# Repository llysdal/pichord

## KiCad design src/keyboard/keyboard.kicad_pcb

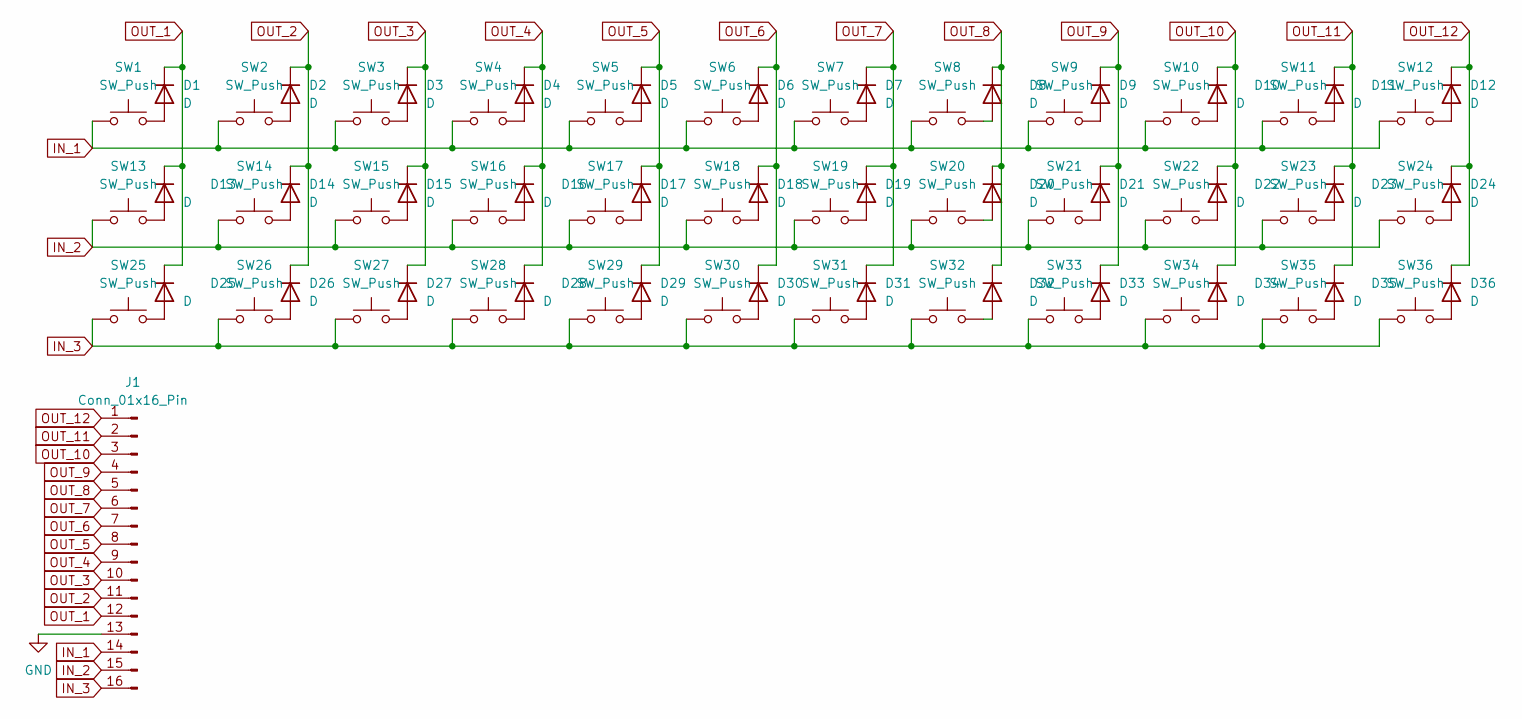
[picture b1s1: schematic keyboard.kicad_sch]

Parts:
D1, D2, D3, D4, D5, D6, D7, D8, D9, D10, D11, D12, D13, D14, D15, D16, D17, D18, D19, D20, D21, D22, D23, D24, D25, D26, D27, D28, D29, D30, D31, D32, D33, D34, D35, D36: D; D_DO-35_SOD27_P7.62mm_Horizontal
J1: Conn_01x16_Pin; PinHeader_2x08_P2.54mm_Vertical
SW1, SW2, SW3, SW4, SW5, SW6, SW7, SW8, SW9, SW10, SW11, SW12, SW13, SW14, SW15, SW16, SW17, SW18, SW19, SW20, SW21, SW22, SW23, SW24, SW25, SW26, SW27, SW28, SW29, SW30, SW31, SW32, SW33, SW34, SW35, SW36: SW_Push; Kailh_socket_MX_platemount

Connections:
GND: J1.13
IN_1: J1.14, SW1.1, SW2.1, SW3.1, SW4.1, SW5.1, SW6.1, SW7.1, SW8.1, SW9.1, SW10.1, SW11.1, SW12.1
IN_2: J1.15, SW13.1, SW14.1, SW15.1, SW16.1, SW17.1, SW18.1, SW19.1, SW20.1, SW21.1, SW22.1, SW23.1, SW24.1
IN_3: J1.16, SW25.1, SW26.1, SW27.1, SW28.1, SW29.1, SW30.1, SW31.1, SW32.1, SW33.1, SW34.1, SW35.1, SW36.1
unnamed: D1.2 (A), SW1.2
unnamed: D2.2 (A), SW2.2
unnamed: D3.2 (A), SW3.2
unnamed: D4.2 (A), SW4.2
unnamed: D5.2 (A), SW5.2
unnamed: D6.2 (A), SW6.2
unnamed: D7.2 (A), SW7.2
unnamed: D8.2 (A), SW8.2
unnamed: D9.2 (A), SW9.2
unnamed: D10.2 (A), SW10.2
unnamed: D11.2 (A), SW11.2
unnamed: D12.2 (A), SW12.2
unnamed: D13.2 (A), SW13.2
unnamed: D14.2 (A), SW14.2
unnamed: D15.2 (A), SW15.2
unnamed: D16.2 (A), SW16.2
unnamed: D17.2 (A), SW17.2
unnamed: D18.2 (A), SW18.2
unnamed: D19.2 (A), SW19.2
unnamed: D20.2 (A), SW20.2
unnamed: D21.2 (A), SW21.2
unnamed: D22.2 (A), SW22.2
unnamed: D23.2 (A), SW23.2
unnamed: D24.2 (A), SW24.2
unnamed: D25.2 (A), SW25.2
unnamed: D26.2 (A), SW26.2
unnamed: D27.2 (A), SW27.2
unnamed: D28.2 (A), SW28.2
unnamed: D29.2 (A), SW29.2
unnamed: D30.2 (A), SW30.2
unnamed: D31.2 (A), SW31.2
unnamed: D32.2 (A), SW32.2
unnamed: D33.2 (A), SW33.2
unnamed: D34.2 (A), SW34.2
unnamed: D35.2 (A), SW35.2
unnamed: D36.2 (A), SW36.2
OUT_1: D1.1 (K), D13.1 (K), D25.1 (K), J1.12
OUT_2: D2.1 (K), D14.1 (K), D26.1 (K), J1.11
OUT_3: D3.1 (K), D15.1 (K), D27.1 (K), J1.10
OUT_4: D4.1 (K), D16.1 (K), D28.1 (K), J1.9
OUT_5: D5.1 (K), D17.1 (K), D29.1 (K), J1.8
OUT_6: D6.1 (K), D18.1 (K), D30.1 (K), J1.7
OUT_7: D7.1 (K), D19.1 (K), D31.1 (K), J1.6
OUT_8: D8.1 (K), D20.1 (K), D32.1 (K), J1.5
OUT_9: D9.1 (K), D21.1 (K), D33.1 (K), J1.4
OUT_10: D10.1 (K), D22.1 (K), D34.1 (K), J1.3
OUT_11: D11.1 (K), D23.1 (K), D35.1 (K), J1.2
OUT_12: D12.1 (K), D24.1 (K), D36.1 (K), J1.1

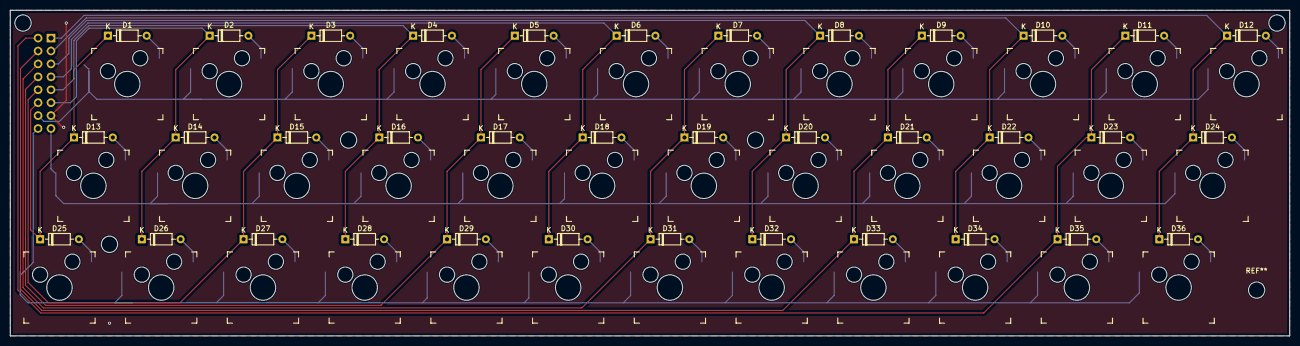
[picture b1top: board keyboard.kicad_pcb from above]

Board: 2 copper layers, 251.5 x 64.0 mm, 73 parts (1 on the bottom side), 51 nets.

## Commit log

2026-02-05 Add low and high pass filters
2026-02-05 Add state saving/loading
2026-02-05 flip sign of triangle to match the rest
2026-02-05 Changed export to be compilable with MPASM
2026-02-10 initial kicad schematic
2026-02-10 add keyboard pcb
2026-02-10 Updated kicad schematic
2026-02-19 Updated gitignore
2026-02-19 Uploaded project files
2026-02-19 Upload appendices
2026-02-19 I2C reading working
